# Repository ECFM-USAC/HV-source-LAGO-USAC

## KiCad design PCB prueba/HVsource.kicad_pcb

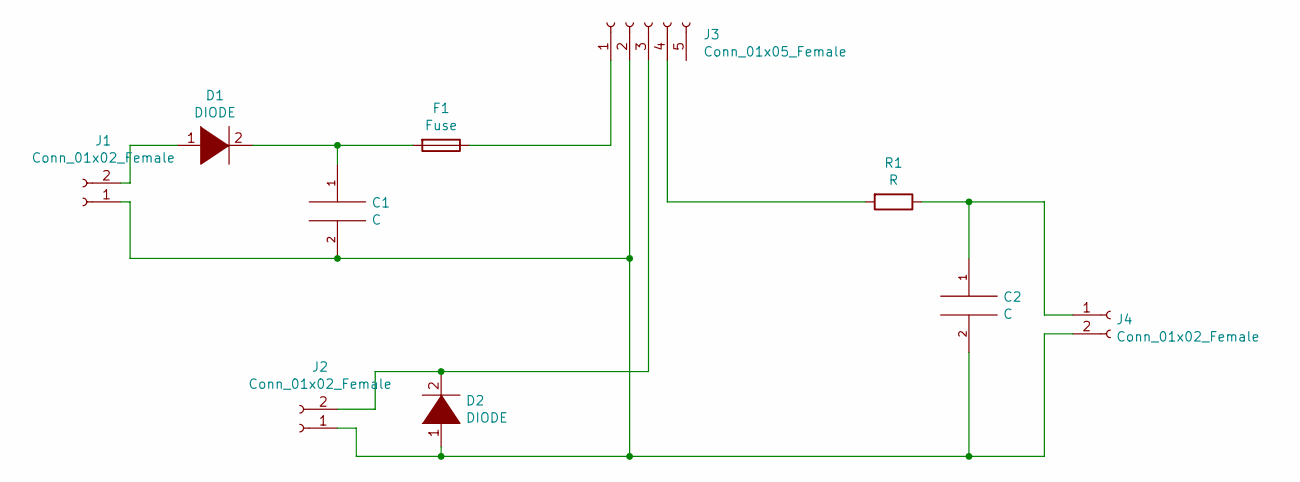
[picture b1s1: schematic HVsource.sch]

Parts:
C1: C; C_Disc_D7.5mm_W5.0mm_P7.50mm
C2: C; C_Disc_D7.5mm_W5.0mm_P10.00mm
D1, D2: DIODE; D_DO-15_P10.16mm_Horizontal
F1: Fuse; D_DO-15_P15.24mm_Horizontal
J1, J2, J4: Conn_01x02_Female; TerminalBlock_Altech_AK300-2_P5.00mm
J3: Conn_01x05_Female; EMCOC20
R1: R; R_Axial_DIN0207_L6.3mm_D2.5mm_P10.16mm_Horizontal

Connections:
unnamed: C1.1, D1.2 (A), F1.2
unnamed: C1.2, C2.2, D2.1 (K), J1.1, J2.1, J3.2, J4.2
unnamed: C2.1, J4.1, R1.1
unnamed: D1.1 (K), J1.2
unnamed: D2.2 (A), J2.2, J3.3
unnamed: F1.1, J3.1
unnamed: J3.4, R1.2

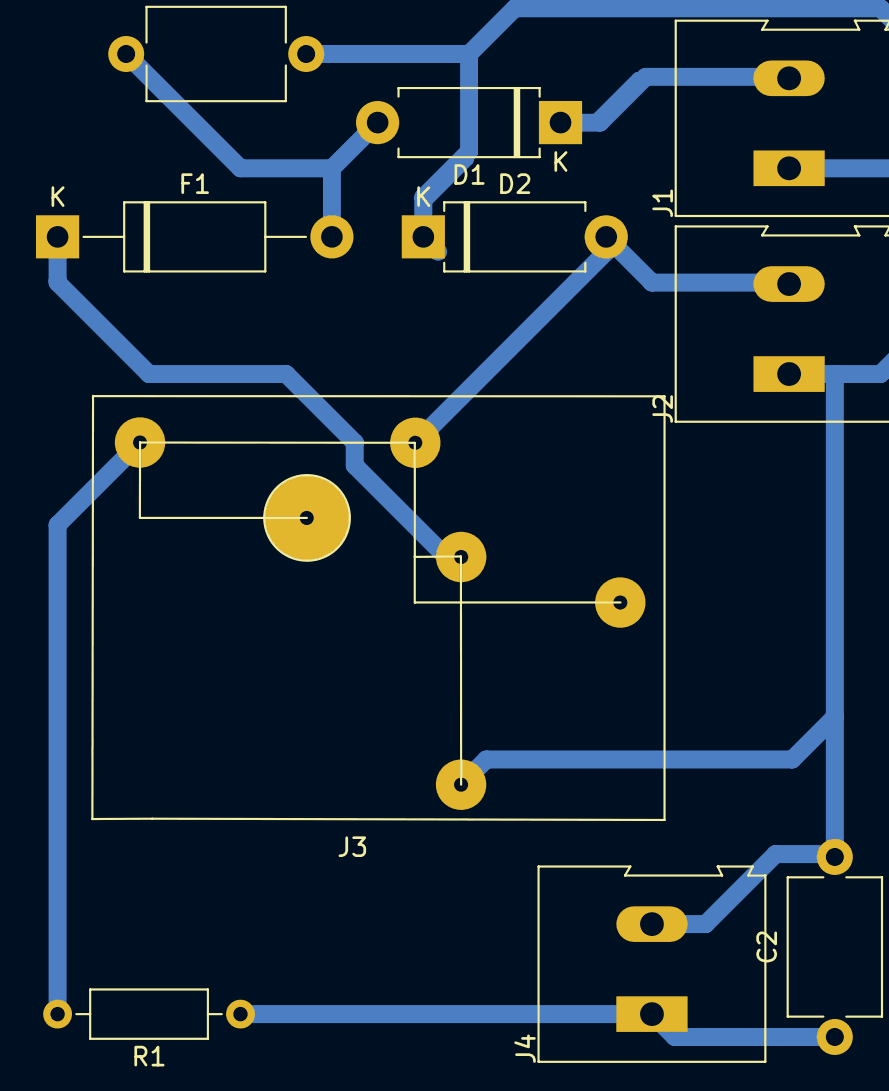
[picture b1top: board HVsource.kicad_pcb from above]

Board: 2 copper layers, 10 parts (0 on the bottom side), 7 nets.

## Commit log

2020-02-17 Create txt
